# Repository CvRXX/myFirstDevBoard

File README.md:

# My first devboard

This devboard is meant to teach computer engineering students of the university of applied sciences to solder and to give them a learning platform to learn embeddded C++. This project is open source and can be found on github: github.com/CvRXX/myFirstDevBoard

## What do you need?
To solder the board you need the following components:

    - The board (I ordered this at jlcpcb.com)
    - 13x 1kΩ resistors
    - 9x RGB LEDS (common annode)
    - 1x arduino nano with pinstrips (optionaly a female strip)
    - 1x passive buzzer
    - 4x push buttons
    - 2x slider switches (2.54mm pin distance)
    - 3x bc550 transistors 
    - 1x 1k pot meter (everything up to 10kΩ)
    - 1x usb cable for the nano
    
## How to solder it?
This readme is not a soldering course so the exact details on how to solder something should be found somewhere else. But I want to give some hints to make your life easier:

    1. Solder the components which are the lowest first (the resistors) and the highest last (the pod meter).
    2. Make sure you put in the leds the right way (long lead in the square hole).
    3. Put headers under the arduino nano so you can use the arduino for others things.
    4. Put the nano with headers on the board and then solder everything in one go.
    
## How to program it?
The one thing that I hate most about of the arduino nano is that they lack a bootloader. The students from Utrecht are lucky beause Florian and I flashed every board already. If you don't have such a nice person nearby you should flash it yourself. This tuturial describes it nicely: https://www.instructables.com/id/How-To-Burn-a-Bootloader-to-Clone-Arduino-Nano-30/.

After that you can use the arduino IDE to flash the board. The students from Utrecht are required to use bmptk & hwlib. 

To find out what is connected to what please read the schematic that's included. You can open this with the free opensource program called kicad (http://kicad.org/).

## I still run into problems, what now?
If you are a student from Utrecht you can go into the turing lab and ask Carlos, Florian or Wouter. If Utrecht is a bit far away from you feel free to email me : myfirstdevboard {at} carlosvanrooijen.nl

## I'm a teacher at an university and I really want to use this, can I?
Sure, love to see my board being used in other places. The only thing that I ask of you is that you retain my name on the board and send me an email that you use it. I only ask for the email because it makes me happy to know that others use it.

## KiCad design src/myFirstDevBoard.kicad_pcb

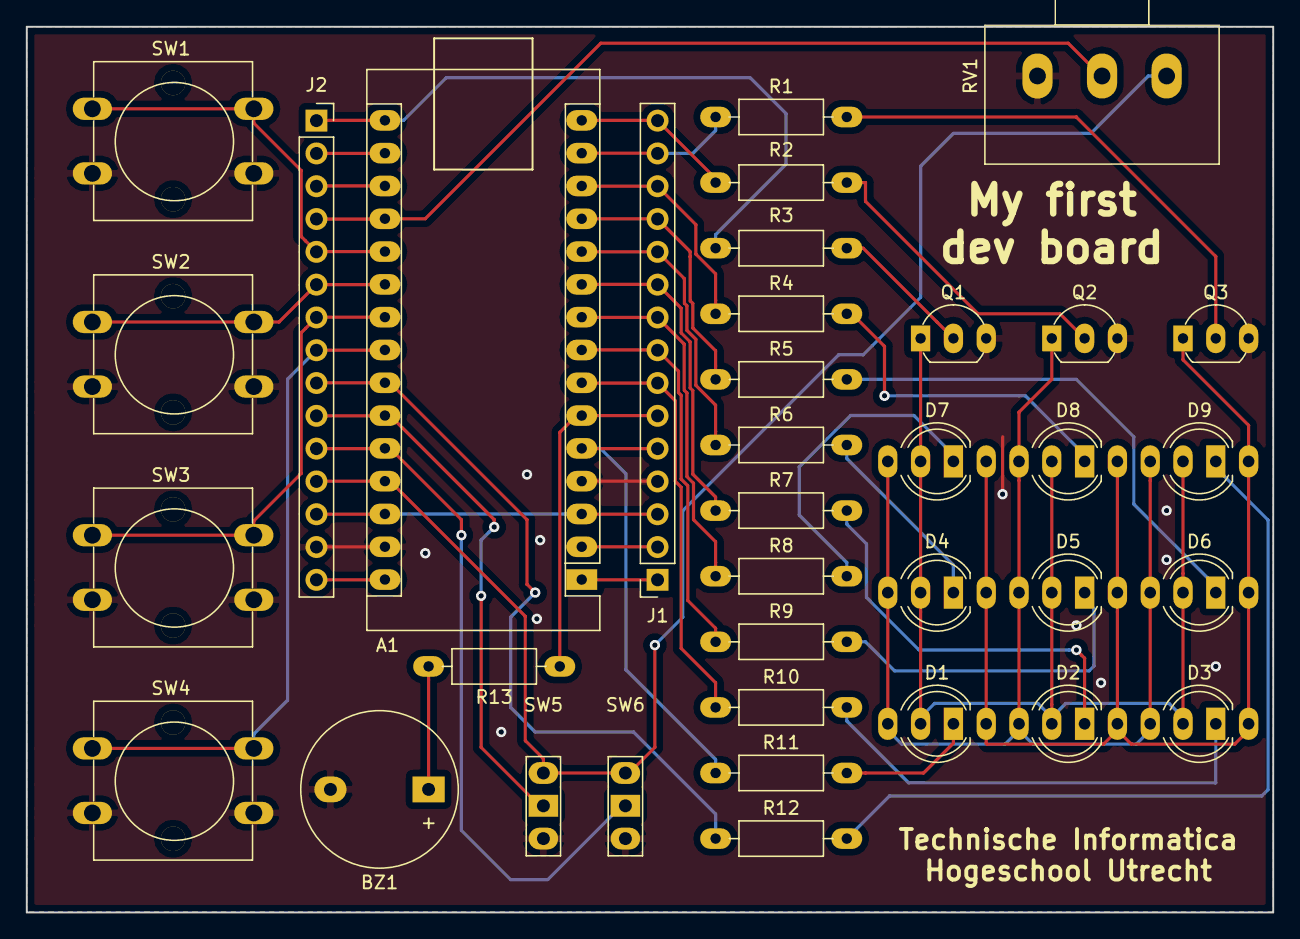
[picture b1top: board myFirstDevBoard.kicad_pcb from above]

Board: 2 copper layers, 96.5 x 68.6 mm, 36 parts (0 on the bottom side), 44 nets.

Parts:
A1: Arduino_Nano_v3.x; Arduino_Nano_oval
BZ1: Buzzer; Buzzer_12x9.5RM7.6_oval
D1, D2, D3, D4, D5, D6, D7, D8, D9: LED_BGRA; LED_D5.0mm-4_RGB_wide
J1, J2: Conn_01x15_Male; PinSocket_1x15_P2.54mm_Vertical
Q1, Q2, Q3: BC550; TO-92_Inline_Wide_oval
R1, R2, R3, R4, R5, R6, R7, R8, R9, R10, R11, R12: 1kΩ; R_Axial_DIN0207_L6.3mm_D2.5mm_P10.16mm_Horizontal_oval
R13: R; R_Axial_DIN0207_L6.3mm_D2.5mm_P10.16mm_Horizontal_oval
RV1: R_POT; Potentiometer_Alps_RK163_Single_Horizontal_oval
SW1, SW2, SW3, SW4: SW_Push; SW_PUSH-12mm_with_poles
SW5, SW6: SW_SLIDER; PinHeader_1x03_P2.54mm_Vertical_oval

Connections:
+3V3: A1.17, J2.2
+5V: A1.27, J2.12, RV1.1, SW5.1, SW6.1
/aref: A1.18, J2.3
/blue: A1.14, J1.14, R1.1
/buzzer: A1.6, J1.6, R13.1
/green: A1.15, J1.15, R2.2
/led1: A1.5, J1.5, R11.1
/led2: A1.7, J1.7, R10.1
/led3: A1.8, J1.8, R9.1
/led4: A1.9, J1.9, R8.1
/led5: A1.10, J1.10, R7.1
/led6: A1.11, J1.11, R6.1
/led7: A1.12, J1.12, R5.1
/led8: A1.13, J1.13, R4.1
/led9: A1.24, J2.9, R12.1
/pot: A1.19, J2.4, RV1.2
/red: A1.16, J2.1, R3.2
/reset: A1.3, A1.28, J1.3, J2.13
/rx: A1.2, J1.2
/sw1: A1.20, J2.5, SW1.1
/sw2: A1.21, J2.6, SW2.1
/sw3: A1.22, J2.7, SW3.1
/sw4: A1.23, J2.8, SW4.1
/sw5: A1.26, J2.11, SW6.2
/sw6: A1.25, J2.10, SW5.2
/tx: A1.1, J1.1
/vin: A1.30, J2.15
GND: A1.4, A1.29, BZ1.2, J1.4, J2.14, Q1.3, Q2.3, Q3.3, RV1.3, SW1.2, SW2.2, SW3.2, SW4.2, SW5.3, SW6.3
unnamed: BZ1.1, R13.2
unnamed: D1.1, D2.1, D3.1, D4.1, D5.1, D6.1, D7.1, D8.1, D9.1, Q1.1
unnamed: D1.2, D2.2, D3.2, D4.2, D5.2, D6.2, D7.2, D8.2, D9.2, Q2.1
unnamed: D1.3, D2.3, D3.3, D4.3, D5.3, D6.3, D7.3, D8.3, D9.3, Q3.1
unnamed: D1.4, R11.2
unnamed: D2.4, R7.2
unnamed: D3.4, R10.2
unnamed: D4.4, R6.2
unnamed: D5.4, R9.2
unnamed: D6.4, R5.2
unnamed: D7.4, R8.2
unnamed: D8.4, R4.2
unnamed: D9.4, R12.2
unnamed: Q1.2, R3.1
unnamed: Q2.2, R2.1
unnamed: Q3.2, R1.2

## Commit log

2019-03-05 making v0.2
2019-03-20 adding v0.03
2019-03-28 changing silkscreen to be organised
2019-03-28 correcting colors
2019-03-28 reorganising schematic
2019-03-28 fixing layout and fixing comments
2019-03-28 fixing silkscreen
2019-03-28 adding buzzer resistor
2019-03-28 adding version 1.00
2019-03-28 updating version number
2019-05-08 prepping for schematic deployment
2019-05-08 Adding readme.md
2020-03-01 changing led silk to right orientation
2020-03-01 moving switch designators up so they are visable above the switches closes #3
2020-03-03 adding link and rubber feet fixing #4 fixing #2
2020-03-03 Revert "adding link and rubber feet" This is reverted because the board is now to big for fab
    This reverts commit 696723d42228766d8a1a20b6e9d58cdf75adf79a.
2020-03-03 adding rubber feet with mounting holes, github link and logso
2020-03-05 setting it to v2.00
2020-04-14 moving pod meter and removing signs on feed to fix #5 and #6
2020-04-14 setting v2.01
2021-11-09 Update README.md
    https://forum.kicad.info/t/warning-avoid-all-links-to-kicad-pcb-org-use-kicad-org/31521
